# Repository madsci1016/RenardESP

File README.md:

# RenardESP
A ESP8266 Wifi Adapter for Renard based Christmas Light Dimmers.

This work is licensed under a Creative Commons Attribution-NonCommercial 4.0 International License.
This work is distributed in the hope that it will be useful, but WITHOUT ANY WARRANTY; without even the implied warranty of MERCHANTABILITY or FITNESS FOR A PARTICULAR PURPOSE.

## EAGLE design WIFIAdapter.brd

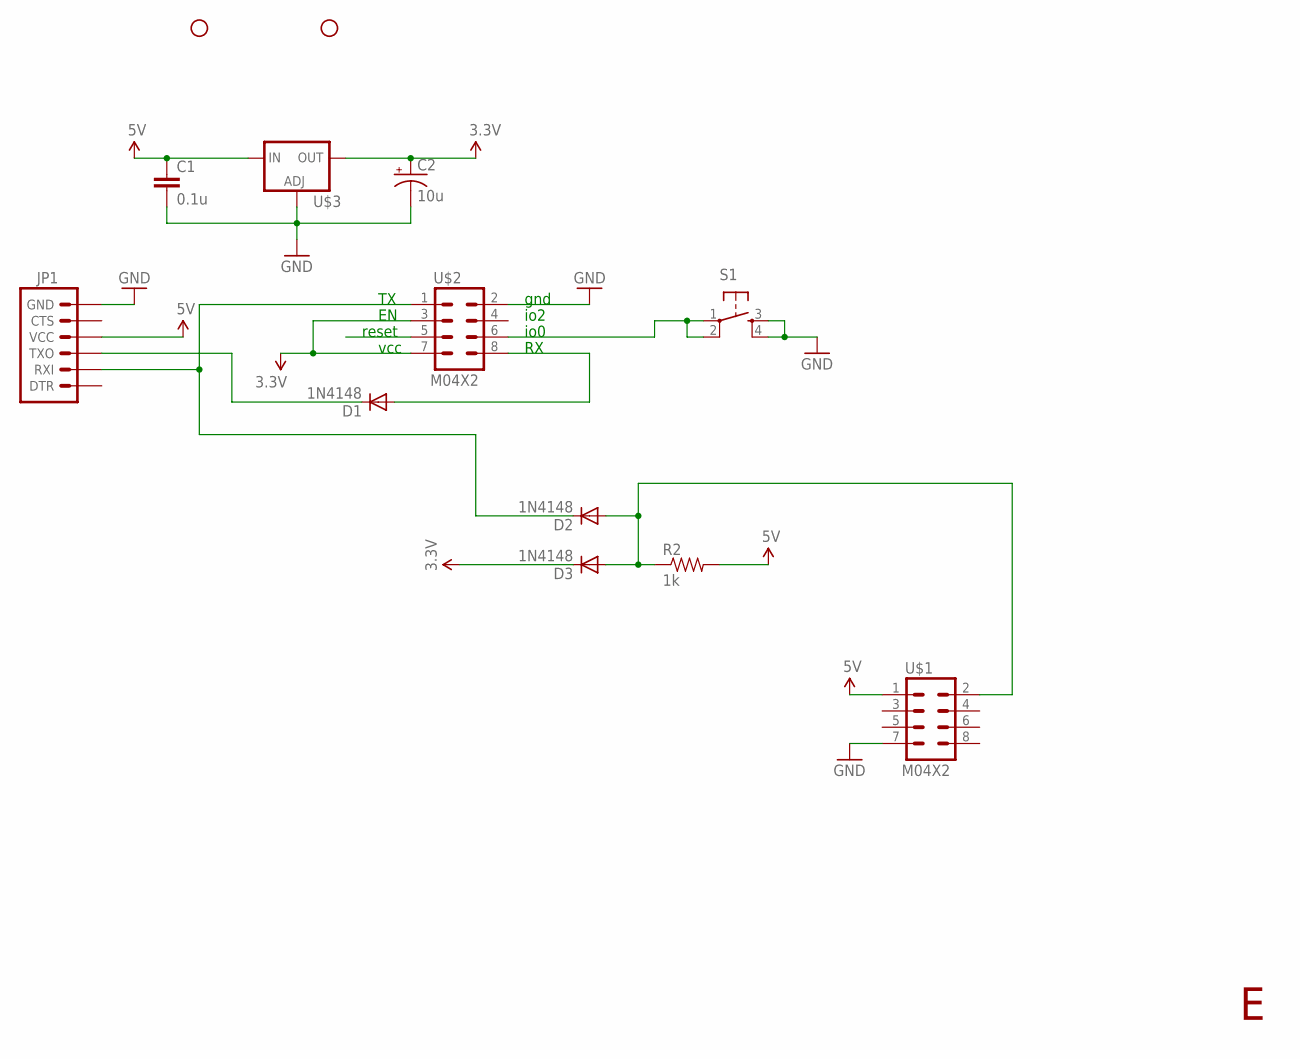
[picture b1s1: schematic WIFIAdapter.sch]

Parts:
C1: 0.1u; CAP-PTH-SMALLEZ
C2: 10u; CPOL-RADIAL-10UF-25V
D1, D2, D3: 1N4148; DO35-7
JP1: ARDUINO_SERIAL_PROGRAMLOCK; 1X06_LOCK
R2: 1k; AXIAL-0.3EZ
S1: TAC_SWITCHPTH; TACTILE-PTH
STANDOFF1, STANDOFF2: STAND-OFFTIGHT; STAND-OFF-TIGHT
U$1, U$2: M04X2; 2X4
U$3: LM317TS; 317TS

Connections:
3.3V: C2.1 (+), D3.C, U$2.3, U$2.7, U$3.2 (OUT)
5V: C1.1, JP1.4 (VCC), R2.P$2 (2), U$1.1, U$3.3 (IN)
GND: C1.2, C2.2 (-), JP1.6 (GND), S1.3, S1.4, U$1.7, U$2.2, U$3.1 (ADJ)
unnamed: S1.1, S1.2, U$2.6
unnamed: D1.C, JP1.3 (TXO)
unnamed: D2.A, D3.A, R2.P$1 (1), U$1.2
RX: D1.A, U$2.8
TX: D2.C, JP1.2 (RXI), U$2.1

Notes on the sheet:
reset
vcc
gnd
io2
io0

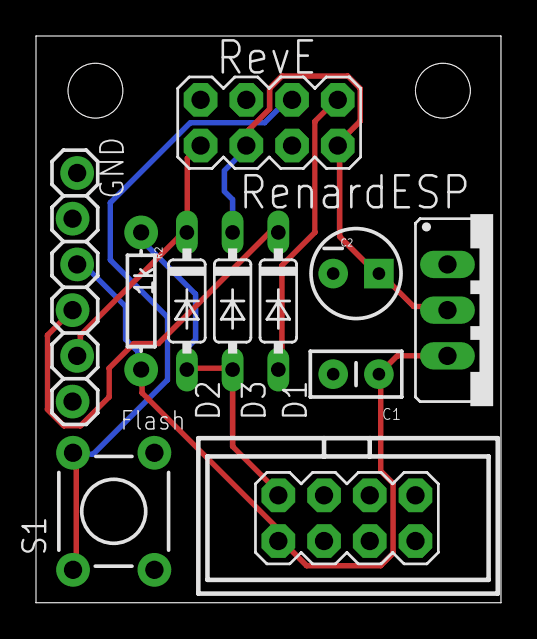
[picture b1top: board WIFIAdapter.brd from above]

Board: 2 copper layers, 25.8 x 31.5 mm, 13 parts (0 on the bottom side), 8 nets.

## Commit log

2015-08-01 Initial Commit
    The Beginning.
2015-08-01 Changed Settings Clear to use IO2
    Changed Setting clear jumper to short IO2 to ground. Turns out there is
    no pulldown resistors in the ESP, so plan to use IO0 twice doesn't work.
2015-08-03 Processed for SeeedStudo PCB service
    Includes CAM files for Seeed
2015-09-22 Changed Capacitor in BOM
    Bigger!
2015-10-16 RevE with 8 pin DIP adapter
    Trade the break away PCB adapter for a COTS ribbon cable DIP adapter.
2015-10-27 Updated BOM
    Now includes button

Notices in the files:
parts and their libraries:
SparkFun-Capacitors: Licensing: Creative Commons ShareAlike 4.0 International - https://creativecommons.org/licenses/by-sa/4.0
